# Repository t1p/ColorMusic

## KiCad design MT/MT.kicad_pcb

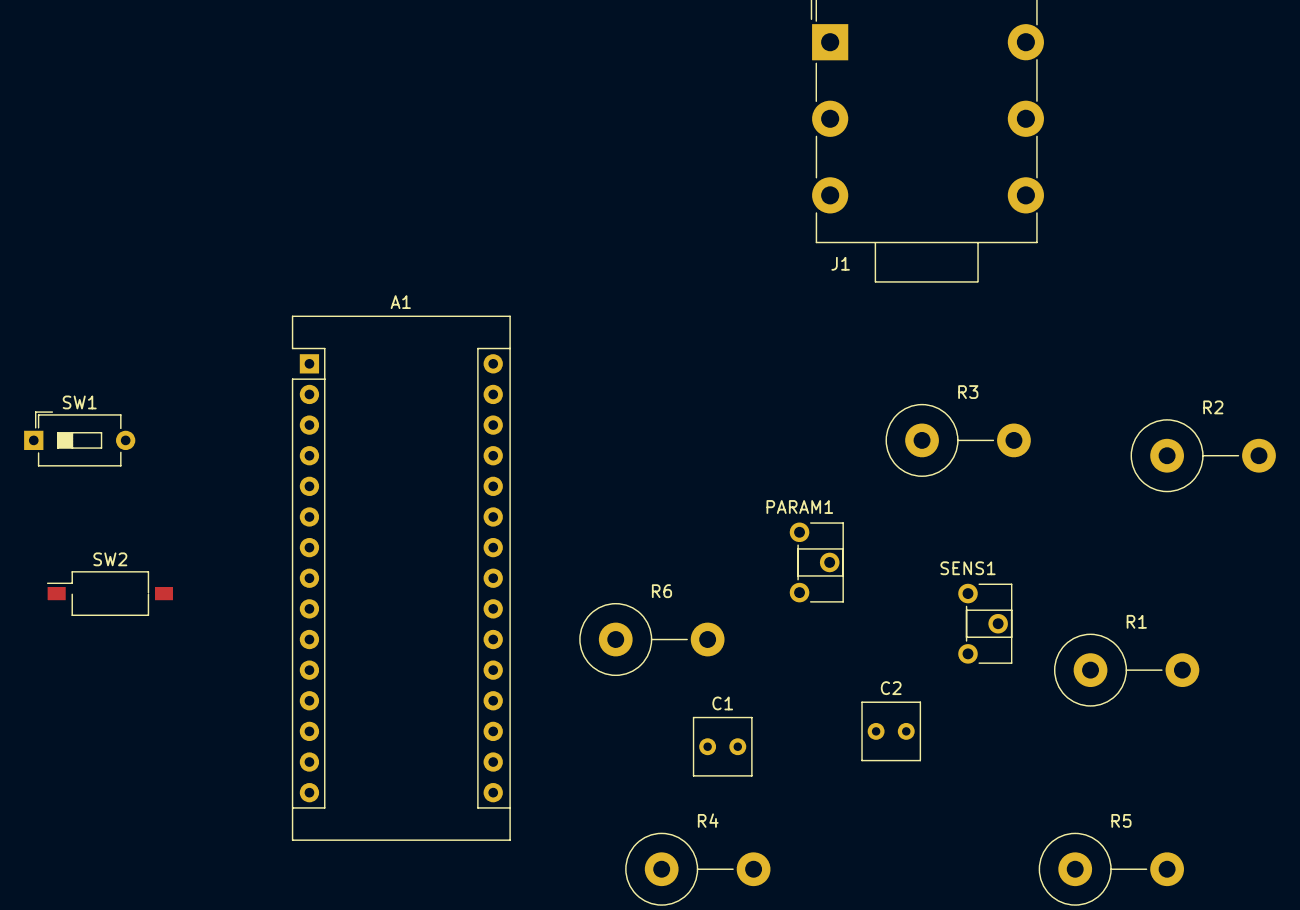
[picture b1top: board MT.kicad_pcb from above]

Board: 2 copper layers, 14 parts (0 on the bottom side), 10 nets, no tracks yet.

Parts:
A1: Arduino_Nano_v3.x; Arduino_Nano
C1: 0.1мкФ; C_Rect_L4.6mm_W4.6mm_P2.50mm_MKS02_FKP02
C2: 10мкФ; C_Rect_L4.6mm_W4.6mm_P2.50mm_MKS02_FKP02
J1: AudioJack3_Ground; Jack_3.5mm_Neutric_NMJ6HCD2_Horizontal
PARAM1: 10K; Potentiometer_ACP_CA6-H2,5_Horizontal
R1, R2: 100K; R_Axial_DIN0614_L14.3mm_D5.7mm_P7.62mm_Vertical
R3, R6: 2K; R_Axial_DIN0614_L14.3mm_D5.7mm_P7.62mm_Vertical
R4, R5: 4.7K; R_Axial_DIN0614_L14.3mm_D5.7mm_P7.62mm_Vertical
SENS1: 10K; Potentiometer_ACP_CA6-H2,5_Horizontal
SW1: PATTERN1; SW_DIP_SPSTx01_Slide_6.7x4.1mm_W7.62mm_P2.54mm_LowProfile
SW2: COLOR1; SW_DIP_SPSTx01_Slide_Omron_A6S-110x_W8.9mm_P2.54mm

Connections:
+5V: A1.27, PARAM1.3, SENS1.3
GND: A1.4, A1.29, C1.2, PARAM1.1, R2.1, R3.1, SW1.1, SW2.1
unnamed: A1.5, SW1.2
unnamed: A1.6, SW2.2
unnamed: A1.18, R6.2
unnamed: A1.19, C1.1, C2.2, R1.1, R2.2
unnamed: A1.20, PARAM1.2
unnamed: C2.1, R4.2, R5.2
unnamed: R1.2, R6.1, SENS1.2
unnamed: R3.2, SENS1.1

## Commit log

2018-11-27 Add KiCad project
2019-06-18 Коды цвета
